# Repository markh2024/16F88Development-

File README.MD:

# Creating a PIC16F88 development board 

## Main Objectives 

The primary objectives of this project were to 

-   Demonstrate Dynamic Control of PORTB Pins:
        Dynamically control PORTB pins (RB0 to RB3) in a sequential manner (left-to-right and right-to-left) with a customizable delay.

-   Utilize Timer0 for Accurate Delay:
        Implement precise timing using the Timer0 peripheral with an interrupt service routine (ISR) to achieve delays.

-   Create a Modular Design:
        Use a header file (port_scan.h) to separate reusable code and configuration settings from the main implementation. This modular design improves code reusability and maintainability.

-   Simplify Configuration for a Microcontroller:
        Set up the internal oscillator for a specific clock frequency (2 MHz) and configure the microcontroller using configuration bits for optimal performance.

-   Provide an Educational Example:
        Serve as an educational guide for beginners in embedded systems to understand the implementation and use of timers, interrupts, and port manipulation in an 8-bit microcontroller.

## Additional objectives 

- To show others how to use  opensource to create schematics and PCB Layouts using Kicad  such that they can work from  home based situations  with  idea of manufacturing  from home  small scale to begin with 

- To introduce insterested parties to embedded electonics and ecourarge growth in these areas of Industry 

### Sofwtare used  for the entire project was open source 

Details as follows 

- Kicad version Application: KiCad

Version: 6.0.11+dfsg-1, release build

Libraries:
	
- wxWidgets 3.2.2
- libcurl/7.88.1 OpenSSL/3.0.15 zlib/1.2.13 brotli/1.0.9 zstd/1.5.4  
- libidn2/2.3.3 libpsl/0.21.2 (+libidn2/2.3.3) libssh2/1.10.0 nghttp2/1.52.0 librtmp/2.3 OpenLDAP/2.5.13

Platform: Linux 6.1.0-28-amd64 x86_64, 64 bit, Little endian, wxGTK, plasma, x11

Build Info:

-   Date: Jan 26 2023 05:35:43  
-   wxWidgets: 3.2.1 (wchar_t,wx containers) GTK+ 3.24
-   Boost: 1.74.0
-   OCC: 7.6.3
-   Curl: 7.87.0
-   ngspice: 38
-   Compiler: GCC 12.2.0 with C++ ABI 1017

Build settings:
-   KICAD_USE_OCC=ON
-   KICAD_SPICE=ON

3D Images of working prototype are below 

- Component side 

- Copper track side   below 

- Schematic  is below 

### Compilers used 

- XC8 MPlabX Picmicrochip free version 
-   Product Version: MPLAB X IDE v6.20
Java: 1.8.0_345; OpenJDK 64-Bit Server VM 25.345-b01
Runtime: OpenJDK Runtime Environment 1.8.0_345-b01
System: Linux version 6.1.0-28-amd64 running on amd64; UTF-8; en_GB (mplab)
User directory: /home/mark/.mplab_ide/dev/v6.20
Cache directory: /home/mark/.cache/mplab_ide/dev/v6.20/var

### Finished PCB assembled and mounted is shown below 

## All files you need are available  within this repro 

Maths for the  calulating timer values and how you arrive at this Ive created in a seperate pdf file  at this  link below 

["Maths for Calculating timer0  values"](maths.pdf)

## Semi final Layout of PCB 

I will be changing this  over the next few weeks buto get you started this is a 
fully working PCB  This was all done using Single sided  for ease and simplicity
so as to  show you what  you can do by hand  without to many problems 

See Image  below of Kicad PCB Layout 

### Please see link below for more in depth notes 

[Aditional note for use with self tutorials and for tutors ](/TutorialNotes.MD)

## Additional references that I sought  on ecountering issues  with MPLabX 

-   (1) How to use libre office for maths equations

https://www.youtube.com/watch?v=LBs6DFoO9dw&t=1802s

-   (2) Unresolved libraries and how to correct 

https://www.youtube.com/watch?v=HvJSqGaQnGM

-   (3)  Using pickit 3 how too's 

https://www.youtube.com/watch?v=UiTKBwKBf6g 

Personal Links  and where you can watch more on how i  made this and wrote code although this is  commented within files 

-    FaceBook 

https://www.facebook.com/mark.harrington.14289/

-    Instagram 

https://www.instagram.com/markukh2021/

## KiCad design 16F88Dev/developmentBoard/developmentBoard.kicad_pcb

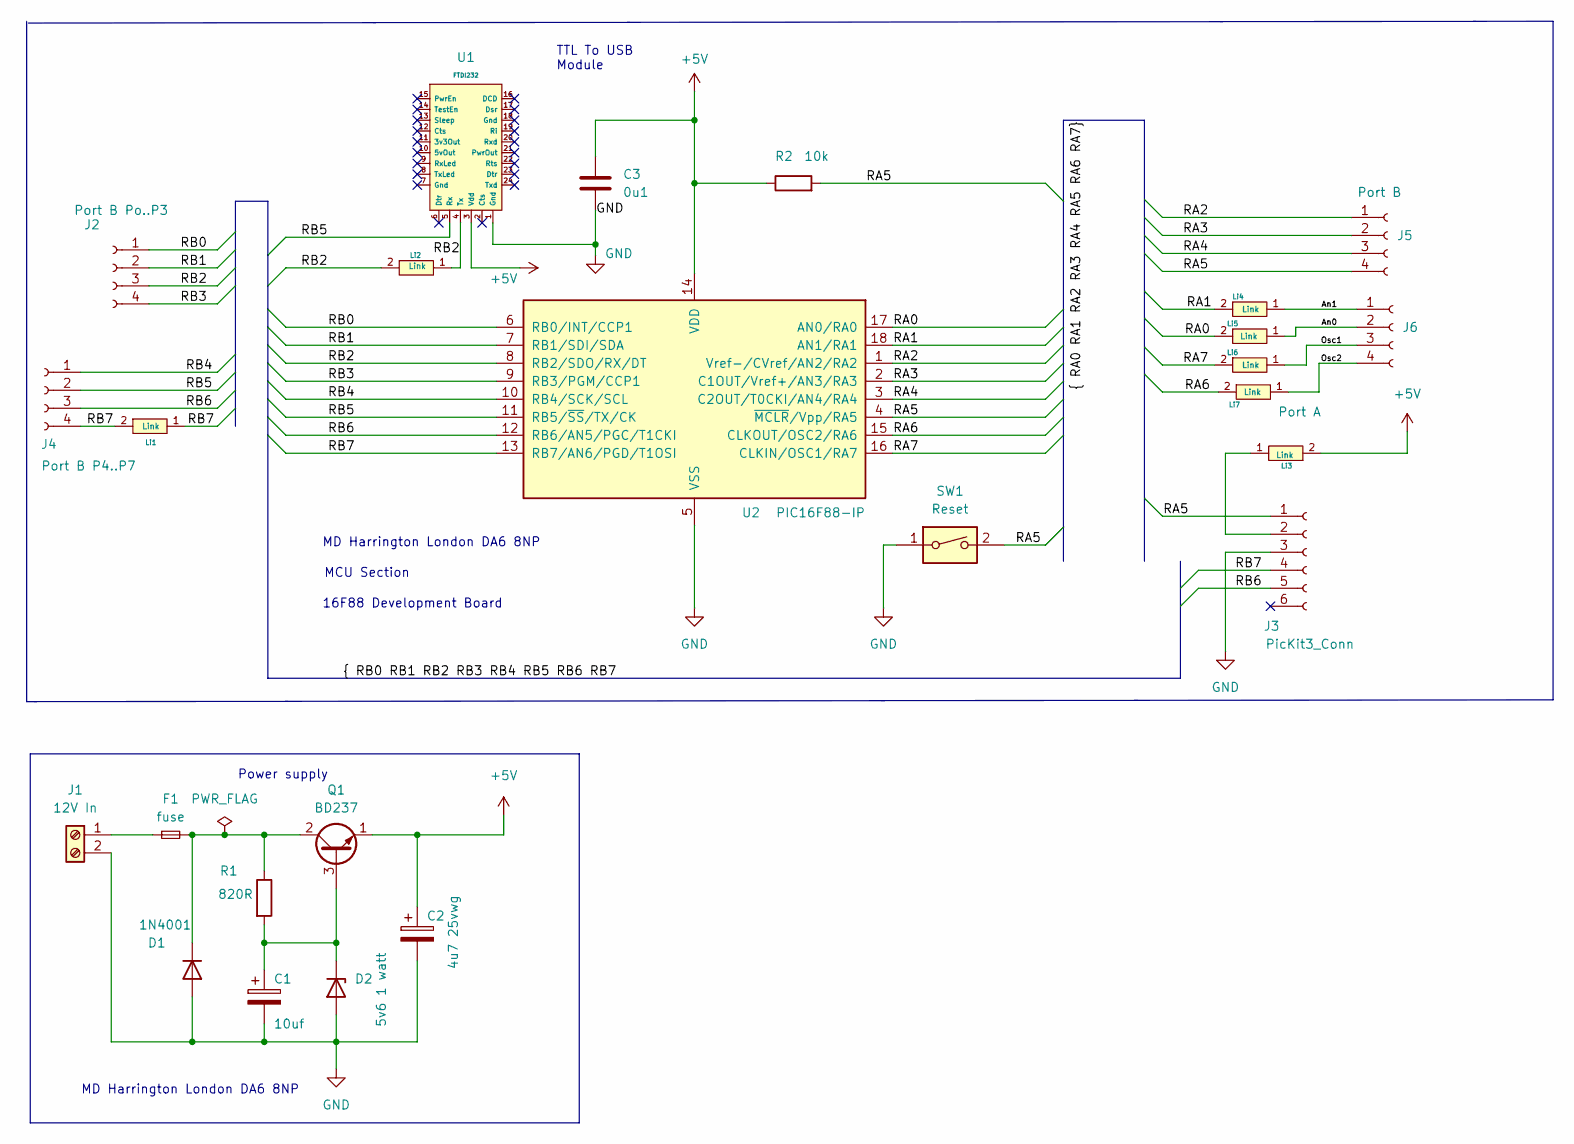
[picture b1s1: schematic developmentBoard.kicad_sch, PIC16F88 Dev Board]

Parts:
C1: 10uf; CP_Radial_D4.0mm_P1.50mm
C2: 4u7 25vwg; CP_Radial_D4.0mm_P1.50mm
C3: 0u1; C_Disc_D3.8mm_W2.6mm_P2.50mm
D1: 1N4001; D_DO-41_SOD81_P7.62mm_Horizontal
D2: 5v6 1 watt; D_A-405_P7.62mm_Horizontal
F1: fuse; R_Axial_DIN0204_L3.6mm_D1.6mm_P2.54mm_Vertical
J1: 12V In; TerminalBlock_bornier-2_P5.08mm
J2: Port B Po..P3; PinSocket_1x04_P2.54mm_Vertical
J3: PicKit3_Conn; PinHeader_1x06_P2.54mm_Horizontal
J4: Port B P4..P7; PinSocket_1x04_P2.54mm_Vertical
J5: Port B; PinSocket_1x04_P2.54mm_Vertical
J6: Port A; PinSocket_1x04_P2.54mm_Vertical
Li1, Li4, Li5, Li6, Li7: Link; Li 5mm
Li2: Link; Li 12mm
Li3: Link; Li 8mm
Q1: BD237; TO-126-3_Vertical
R1: 820R; R_Axial_DIN0207_L6.3mm_D2.5mm_P10.16mm_Horizontal
R2: 10k; R_Axial_DIN0207_L6.3mm_D2.5mm_P10.16mm_Horizontal
SW1: Reset; SW_PUSH_6mm
U1: FTDI232; PinHeader_1x06_P2.54mm_Vertical
U2: PIC16F88-IP; DIP-18_W7.62mm_Socket

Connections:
+5V: C2.1, C3.1, Li3.2, Q1.1 (E), R2.1, U1.3 (Vdd), U2.14 (VDD)
/An0: J6.2, Li5.1
/An1: J6.1, Li4.1
/Osc1: J6.3, Li6.1
/Osc2: J6.4, Li7.1
/RA0: Li5.2, U2.17 (AN0/RA0)
/RA1: Li4.2, U2.18 (AN1/RA1)
/RA2: J5.1, U2.1 (Vref-/CVref/AN2/RA2)
/RA3: J5.2, U2.2 (C1OUT/Vref+/AN3/RA3)
/RA4: J5.3, U2.3 (C2OUT/T0CKI/AN4/RA4)
/RA5: J3.1, J5.4, R2.2, SW1.2, U2.4 (~MCLR/Vpp/RA5)
/RA6: Li7.2, U2.15 (CLKOUT/OSC2/RA6)
/RA7: Li6.2, U2.16 (CLKIN/OSC1/RA7)
/RB0: J2.1, U2.6 (RB0/INT/CCP1)
/RB1: J2.2, U2.7 (RB1/SDI/SDA)
/RB2: J2.3, Li2.1, Li2.2, U1.4 (Tx), U2.8 (RB2/SDO/RX/DT)
/RB3: J2.4, U2.9 (RB3/PGM/CCP1)
/RB4: J4.1, U2.10 (RB4/SCK/SCL)
/RB5: J4.2, U1.5 (Rx), U2.11 (RB5/~SS/TX/CK)
/RB6: J3.5, J4.3, U2.12 (RB6/AN5/PGC/T1CKI)
/RB7: J3.4, J4.4, Li1.1, Li1.2, U2.13 (RB7/AN6/PGD/T1OSI)
GND: C1.2, C2.2, C3.2, D1.2 (A), D2.2 (A), J1.2, J3.3, SW1.1, U1.1 (Gnd), U2.5 (VSS)
unnamed: C1.1, D2.1 (K), Q1.3 (B), R1.2
unnamed: D1.1 (K), F1.2, Q1.2 (C), R1.1
unnamed: F1.1, J1.1
unnamed: J3.2, Li3.1

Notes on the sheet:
16F88 Development Board
TTL To USB Module
MD Harrington London DA6 8NP
Power supply
MCU Section

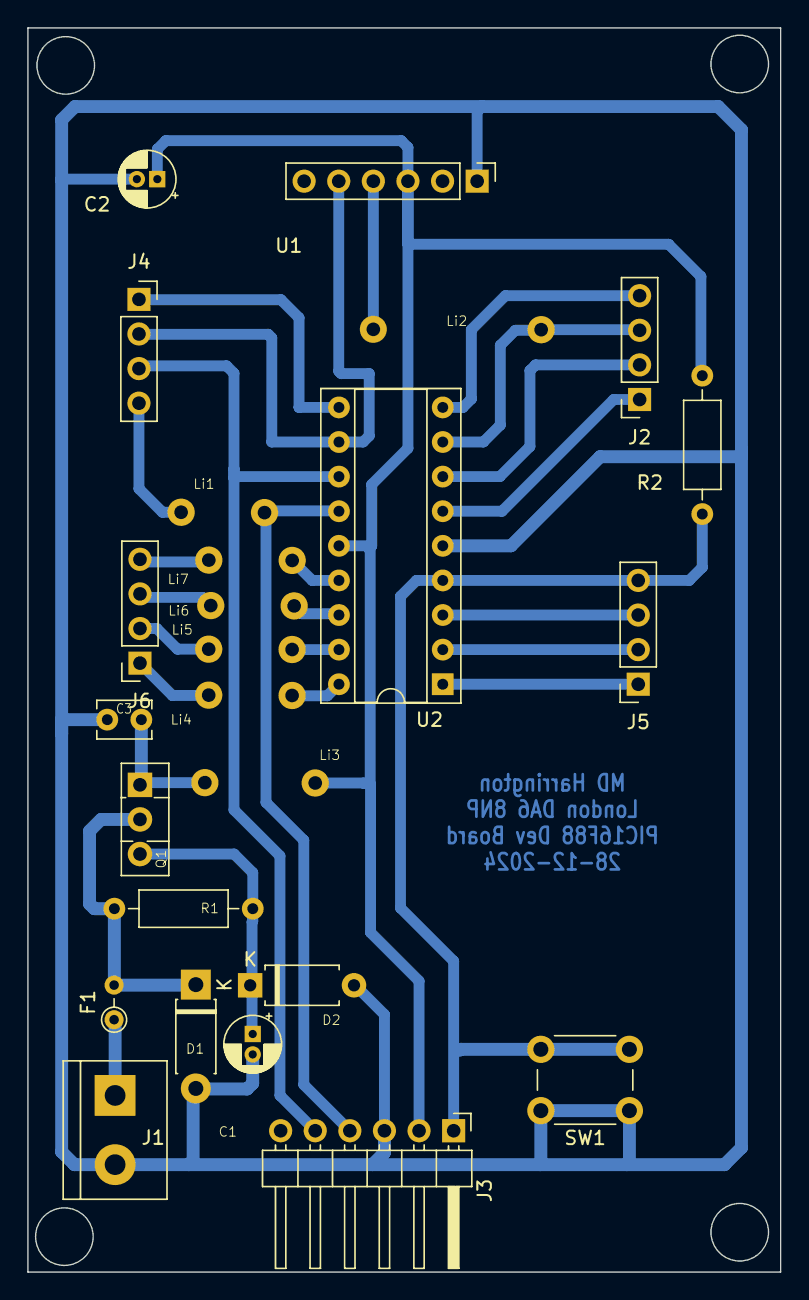
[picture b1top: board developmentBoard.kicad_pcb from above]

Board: 2 copper layers, 55.2 x 91.3 mm, 25 parts (0 on the bottom side), 26 nets.

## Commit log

2025-01-05 Add README.MD and maths.pdf updated
    This will still be undergoing updates over the next few days or so
2025-01-05 Updated images
    Missing Image now added for read me purposes
2025-01-05 Updated
    As per comments on face book and Instagram I will be updating this from time to time to reflect other operations
2025-01-06 Alter and Add tutorial notes
    Tutorial notes well have additional changes over this week
2025-01-08 Add files via upload
    Tutorial notes upgraded to next step and have included data-sheet in pic 16f88
2025-01-09 Add files via upload
    Finalised
